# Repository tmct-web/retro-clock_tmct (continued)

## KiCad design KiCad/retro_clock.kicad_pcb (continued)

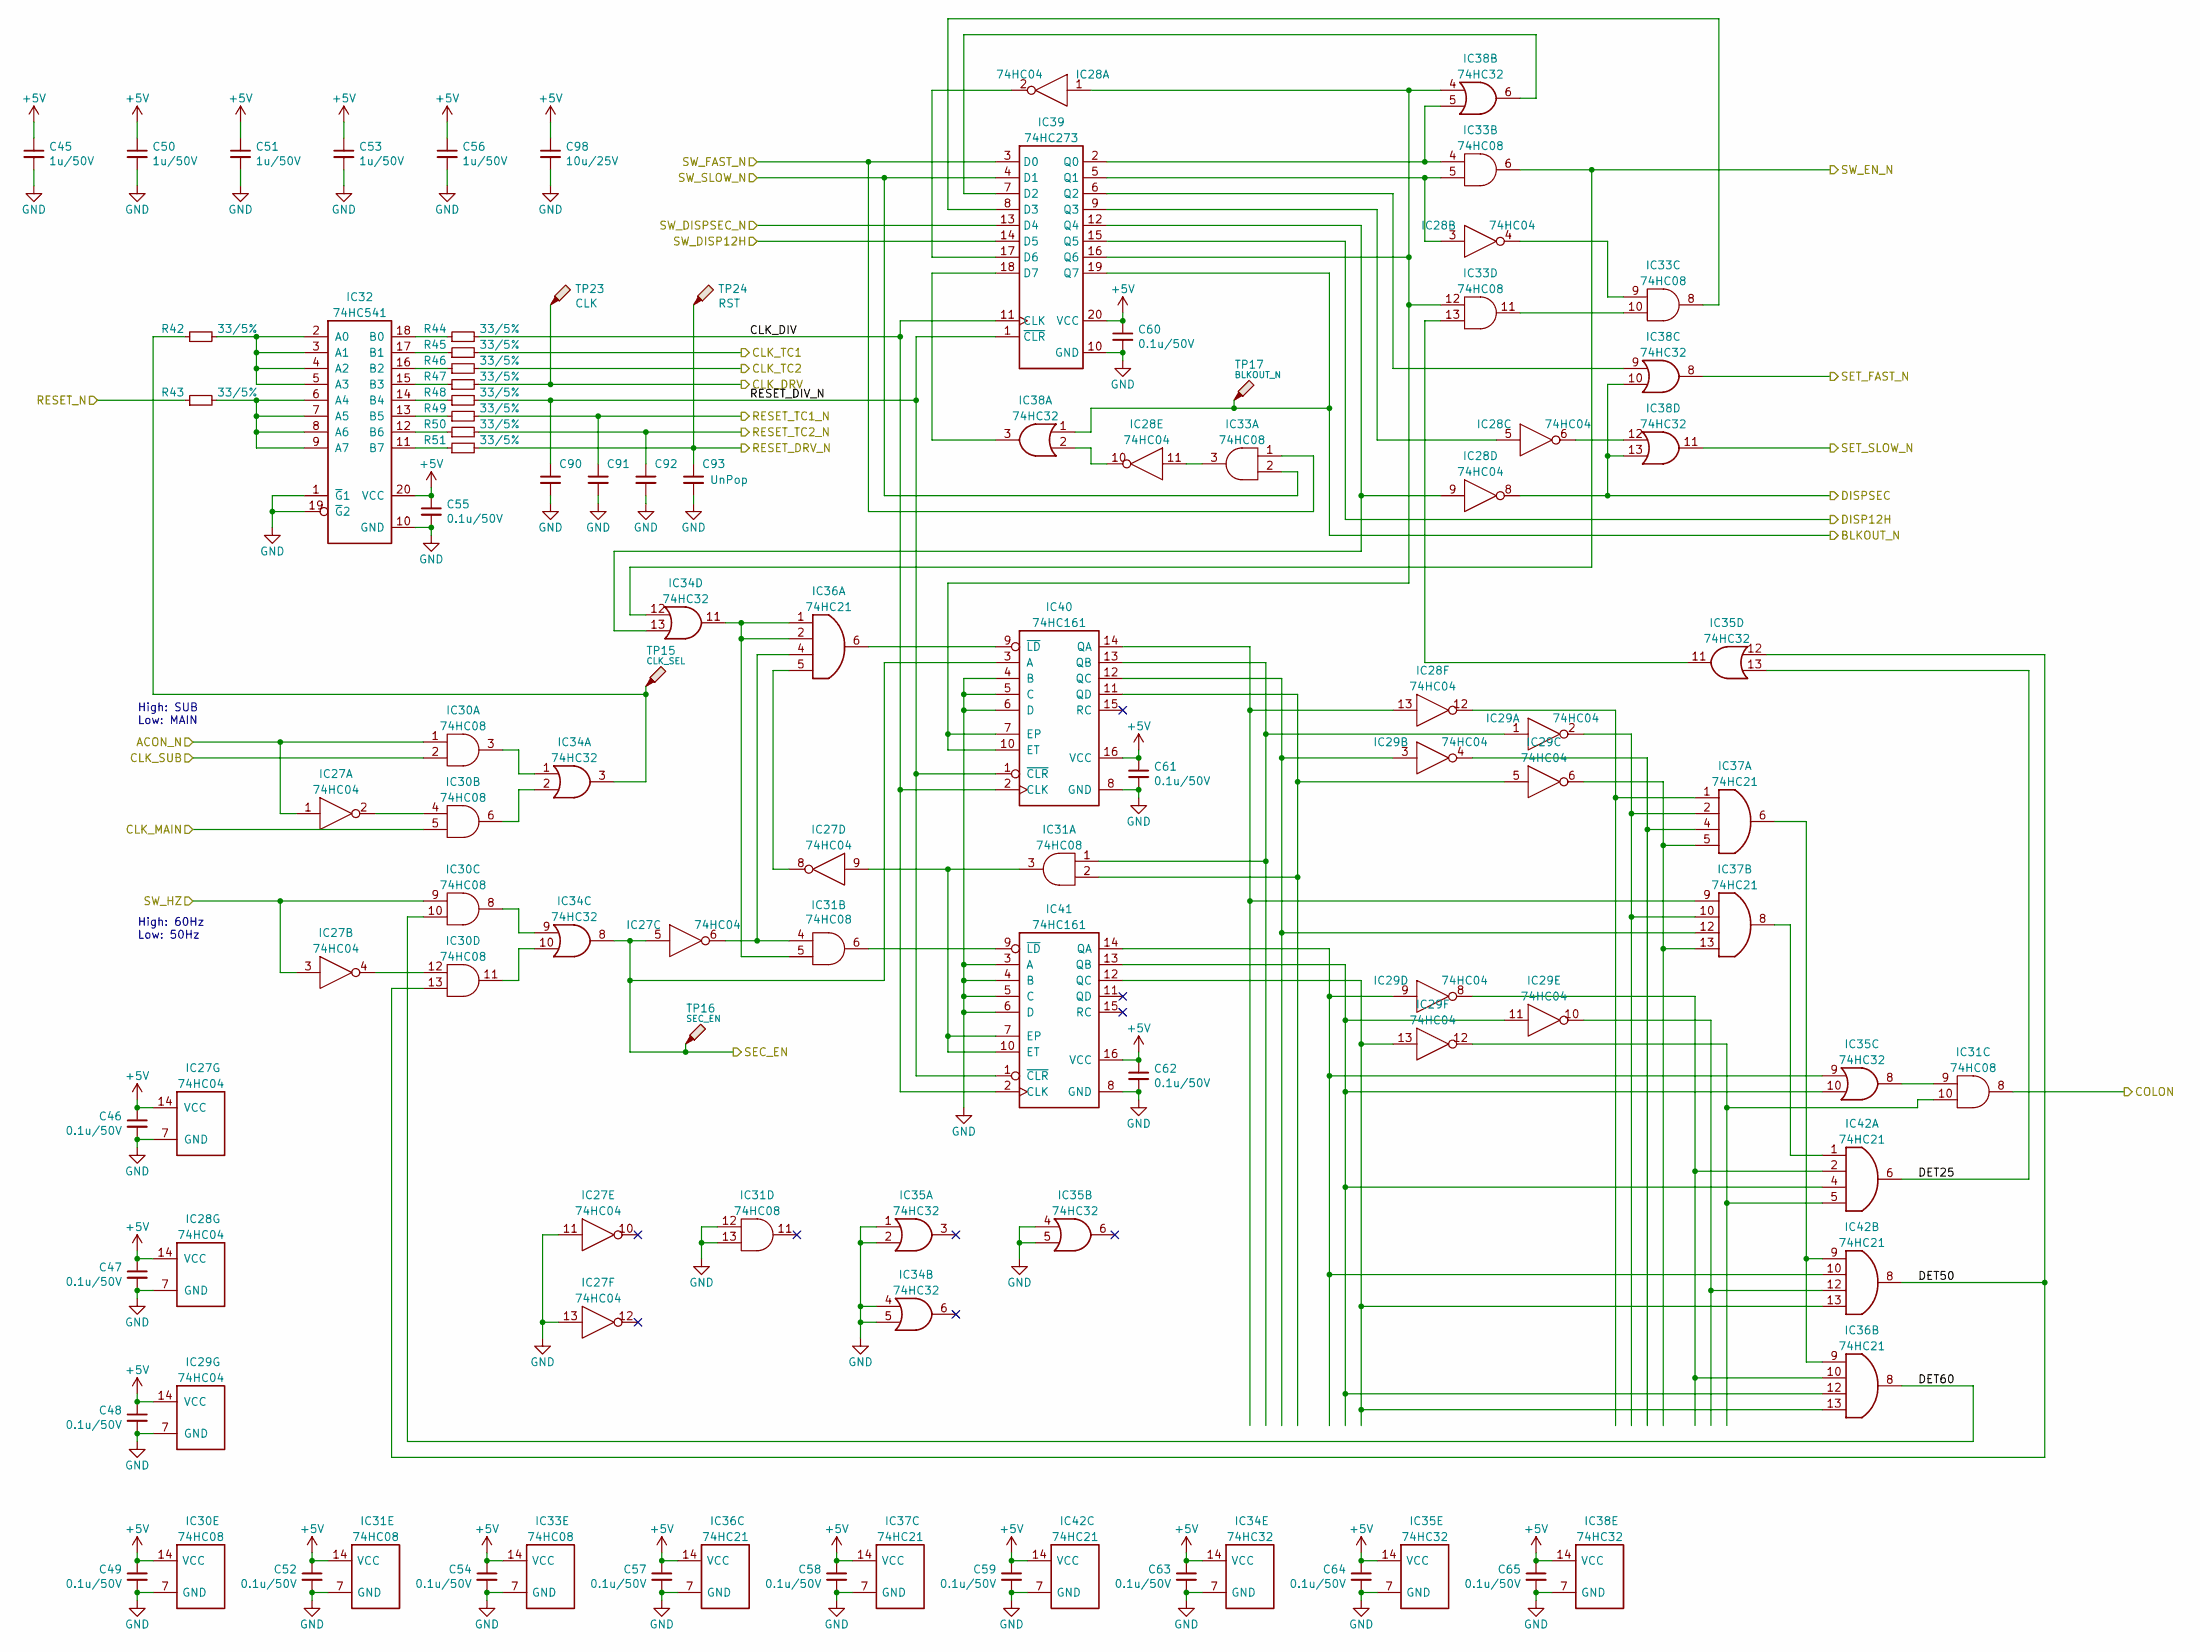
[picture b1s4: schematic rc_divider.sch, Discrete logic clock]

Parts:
C45, C50, C51, C53, C56: 1u/50V; C_Disc_P2.50mm
C46, C47, C48, C49, C52, C54, C55, C57, C58, C59, C60, C61, C62, C63, C64, C65: 0.1u/50V; C_Disc_P2.50mm
C90, C91, C92, C93: UnPop; C_Disc_P2.50mm
C98: 10u/25V; C_Disc_P5.00mm
IC27, IC28, IC29: 74HC04; DIP-14_W7.62mm_Socket_LongPads
IC30, IC31, IC33: 74HC08; DIP-14_W7.62mm_Socket_LongPads
IC32: 74HC541; DIP-20_W7.62mm_Socket_LongPads
IC34, IC35, IC38: 74HC32; DIP-14_W7.62mm_Socket_LongPads
IC36, IC37, IC42: 74HC21; DIP-14_W7.62mm_Socket_LongPads
IC39: 74HC273; DIP-20_W7.62mm_Socket_LongPads
IC40, IC41: 74HC161; DIP-16_W7.62mm_Socket_LongPads
R42, R43, R44, R45, R46, R47, R48, R49, R50, R51: 33/5%; R_Axial_P5.08mm_Horizontal
TP15: CLK_SEL; TestPoint_THTPad_1.5x1.5mm_Drill0.7mm
TP16: SEC_EN; TestPoint_THTPad_1.5x1.5mm_Drill0.7mm
TP17: BLKOUT_N; TestPoint_THTPad_1.5x1.5mm_Drill0.7mm
TP23: CLK; TestPoint_Loop_D2.60mm_Drill0.9mm_Beaded
TP24: RST; TestPoint_Loop_D2.60mm_Drill0.9mm_Beaded

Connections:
+5V: C45.1, C46.1, C47.1, C48.1, C49.1, C50.1, C51.1, C52.1, C53.1, C54.1, C55.1, C56.1, C57.1, C58.1, C59.1, C60.1, C61.1, C62.1, C63.1, C64.1, C65.1, C98.1, IC27.14 (VCC), IC28.14 (VCC), IC29.14 (VCC), IC30.14 (VCC), IC31.14 (VCC), IC32.20 (VCC), IC33.14 (VCC), IC34.14 (VCC), IC35.14 (VCC), IC36.14 (VCC), IC37.14 (VCC), IC38.14 (VCC), IC39.20 (VCC), IC40.16 (VCC), IC41.16 (VCC), IC42.14 (VCC); also elsewhere on the board
/Divider block/ACON_N: IC27.1, IC30.1; also elsewhere on the board
/Divider block/BLKOUT_N: IC38.1, IC39.19 (Q7), TP17.1; also elsewhere on the board
/Divider block/CLK_DIV: IC39.11 (CLK), IC40.2 (CLK), IC41.2 (CLK), R44.2
/Divider block/CLK_MAIN: IC30.5; also elsewhere on the board
/Divider block/CLK_SUB: IC30.2; also elsewhere on the board
/Divider block/COLON: IC31.8; also elsewhere on the board
/Divider block/DET25: IC35.13, IC42.6
/Divider block/DET50: IC30.13, IC35.12, IC42.8
/Divider block/DET60: IC30.10, IC36.8
/Divider block/DISP12H: IC39.15 (Q5); also elsewhere on the board
/Divider block/DISPSEC: IC28.8, IC38.10, IC38.13; also elsewhere on the board
/Divider block/RESET_DIV_N: C90.1, IC39.1 (~CLR), IC40.1 (~CLR), IC41.1 (~CLR), R48.2
/Divider block/RESET_DRV_N: C93.1, R51.2, TP24.1; also elsewhere on the board
/Divider block/RESET_N: R43.1; also elsewhere on the board
/Divider block/SEC_EN: IC27.5, IC34.8, IC40.3 (A), TP16.1; also elsewhere on the board
/Divider block/SET_FAST_N: IC38.8; also elsewhere on the board
/Divider block/SET_SLOW_N: IC38.11; also elsewhere on the board
/Divider block/SW_DISP12H: IC39.14 (D5); also elsewhere on the board
/Divider block/SW_DISPSEC_N: IC39.13 (D4); also elsewhere on the board
/Divider block/SW_FAST_N: IC33.1, IC39.3 (D0); also elsewhere on the board
/Divider block/SW_HZ: IC27.3, IC30.9; also elsewhere on the board
/Divider block/SW_SLOW_N: IC33.2, IC39.4 (D1); also elsewhere on the board
/Driver block/CLK: R47.2, TP23.1; also elsewhere on the board
/Time count block/CLK1: R45.2; also elsewhere on the board
/Time count block/CLK2: R46.2; also elsewhere on the board
/Time count block/RESET1_N: C91.1, R49.2; also elsewhere on the board
/Time count block/RESET2_N: C92.1, R50.2; also elsewhere on the board
/Time count block/SET_EN_N: IC33.6, IC34.12; also elsewhere on the board
GND: C45.2, C46.2, C47.2, C48.2, C49.2, C50.2, C51.2, C52.2, C53.2, C54.2, C55.2, C56.2, C57.2, C58.2, C59.2, C60.2, C61.2, C62.2, C63.2, C64.2, C65.2, C90.2, C91.2, C92.2, C93.2, C98.2, IC27.7 (GND), IC27.11, IC27.13, IC28.7 (GND), IC29.7 (GND), IC30.7 (GND), IC31.7 (GND), IC31.12, IC31.13, IC32.1 (~G~1), IC32.10 (GND), IC32.19 (~G~2), IC33.7 (GND), IC34.4, IC34.5, IC34.7 (GND), IC35.1, IC35.2, IC35.4, IC35.5, IC35.7 (GND), IC36.7 (GND), IC37.7 (GND), IC38.7 (GND), IC39.10 (GND), IC40.4 (B), IC40.5 (C), IC40.6 (D), IC40.8 (GND), IC41.3 (A), IC41.4 (B), IC41.5 (C), IC41.6 (D), IC41.8 (GND), IC42.7 (GND); also elsewhere on the board
unnamed: IC27.2, IC30.4
unnamed: IC27.4, IC30.12
unnamed: IC27.6, IC31.4, IC36.4
unnamed: IC27.8, IC36.5
unnamed: IC27.9, IC31.3, IC41.7 (EP), IC41.10 (ET)
unnamed: IC28.1, IC33.12, IC38.4, IC39.16 (Q6), IC40.7 (EP), IC40.10 (ET)
unnamed: IC28.2, IC39.17 (D6)
unnamed: IC28.3, IC33.5, IC39.5 (Q1)
unnamed: IC28.4, IC33.9
unnamed: IC28.5, IC39.9 (Q3)
unnamed: IC28.6, IC38.12
unnamed: IC28.9, IC34.13, IC39.12 (Q4)
unnamed: IC28.10, IC38.2
unnamed: IC28.11, IC33.3
unnamed: IC28.12, IC37.1
unnamed: IC28.13, IC37.9, IC40.14 (QA)
unnamed: IC29.1, IC31.1, IC40.13 (QB)
unnamed: IC29.2, IC37.2, IC37.10
unnamed: IC29.3, IC37.12, IC40.12 (QC)
unnamed: IC29.4, IC37.4
unnamed: IC29.5, IC31.2, IC40.11 (QD)
unnamed: IC29.6, IC37.5, IC37.13
unnamed: IC29.8, IC36.10, IC42.2
unnamed: IC29.9, IC35.9, IC41.14 (QA), IC42.10
unnamed: IC29.10, IC42.12
unnamed: IC29.11, IC35.10, IC36.12, IC41.13 (QB), IC42.4
unnamed: IC29.12, IC31.10, IC42.5
unnamed: IC29.13, IC36.13, IC41.12 (QC), IC42.13
unnamed: IC30.3, IC34.1
unnamed: IC30.6, IC34.2
unnamed: IC30.8, IC34.9
unnamed: IC30.11, IC34.10
unnamed: IC31.5, IC34.11, IC36.1, IC36.2
unnamed: IC31.6, IC41.9 (~LD)
unnamed: IC31.9, IC35.8
unnamed: IC32.2 (A0), IC32.3 (A1), IC32.4 (A2), IC32.5 (A3), R42.2
unnamed: IC32.6 (A4), IC32.7 (A5), IC32.8 (A6), IC32.9 (A7), R43.2
unnamed: IC32.11 (B7), R51.1
unnamed: IC32.12 (B6), R50.1
unnamed: IC32.13 (B5), R49.1
unnamed: IC32.14 (B4), R48.1
unnamed: IC32.15 (B3), R47.1
unnamed: IC32.16 (B2), R46.1
unnamed: IC32.17 (B1), R45.1
unnamed: IC32.18 (B0), R44.1
unnamed: IC33.4, IC38.5, IC39.2 (Q0)
unnamed: IC33.8, IC39.8 (D3)
unnamed: IC33.10, IC33.11
unnamed: IC33.13, IC35.11
unnamed: IC34.3, R42.1, TP15.1
unnamed: IC36.6, IC40.9 (~LD)
unnamed: IC36.9, IC37.6, IC42.9
unnamed: IC37.8, IC42.1
unnamed: IC38.3, IC39.18 (D7)
unnamed: IC38.6, IC39.7 (D2)
unnamed: IC38.9, IC39.6 (Q2)

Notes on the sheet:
High: 60Hz Low: 50Hz
High: SUB Low: MAIN

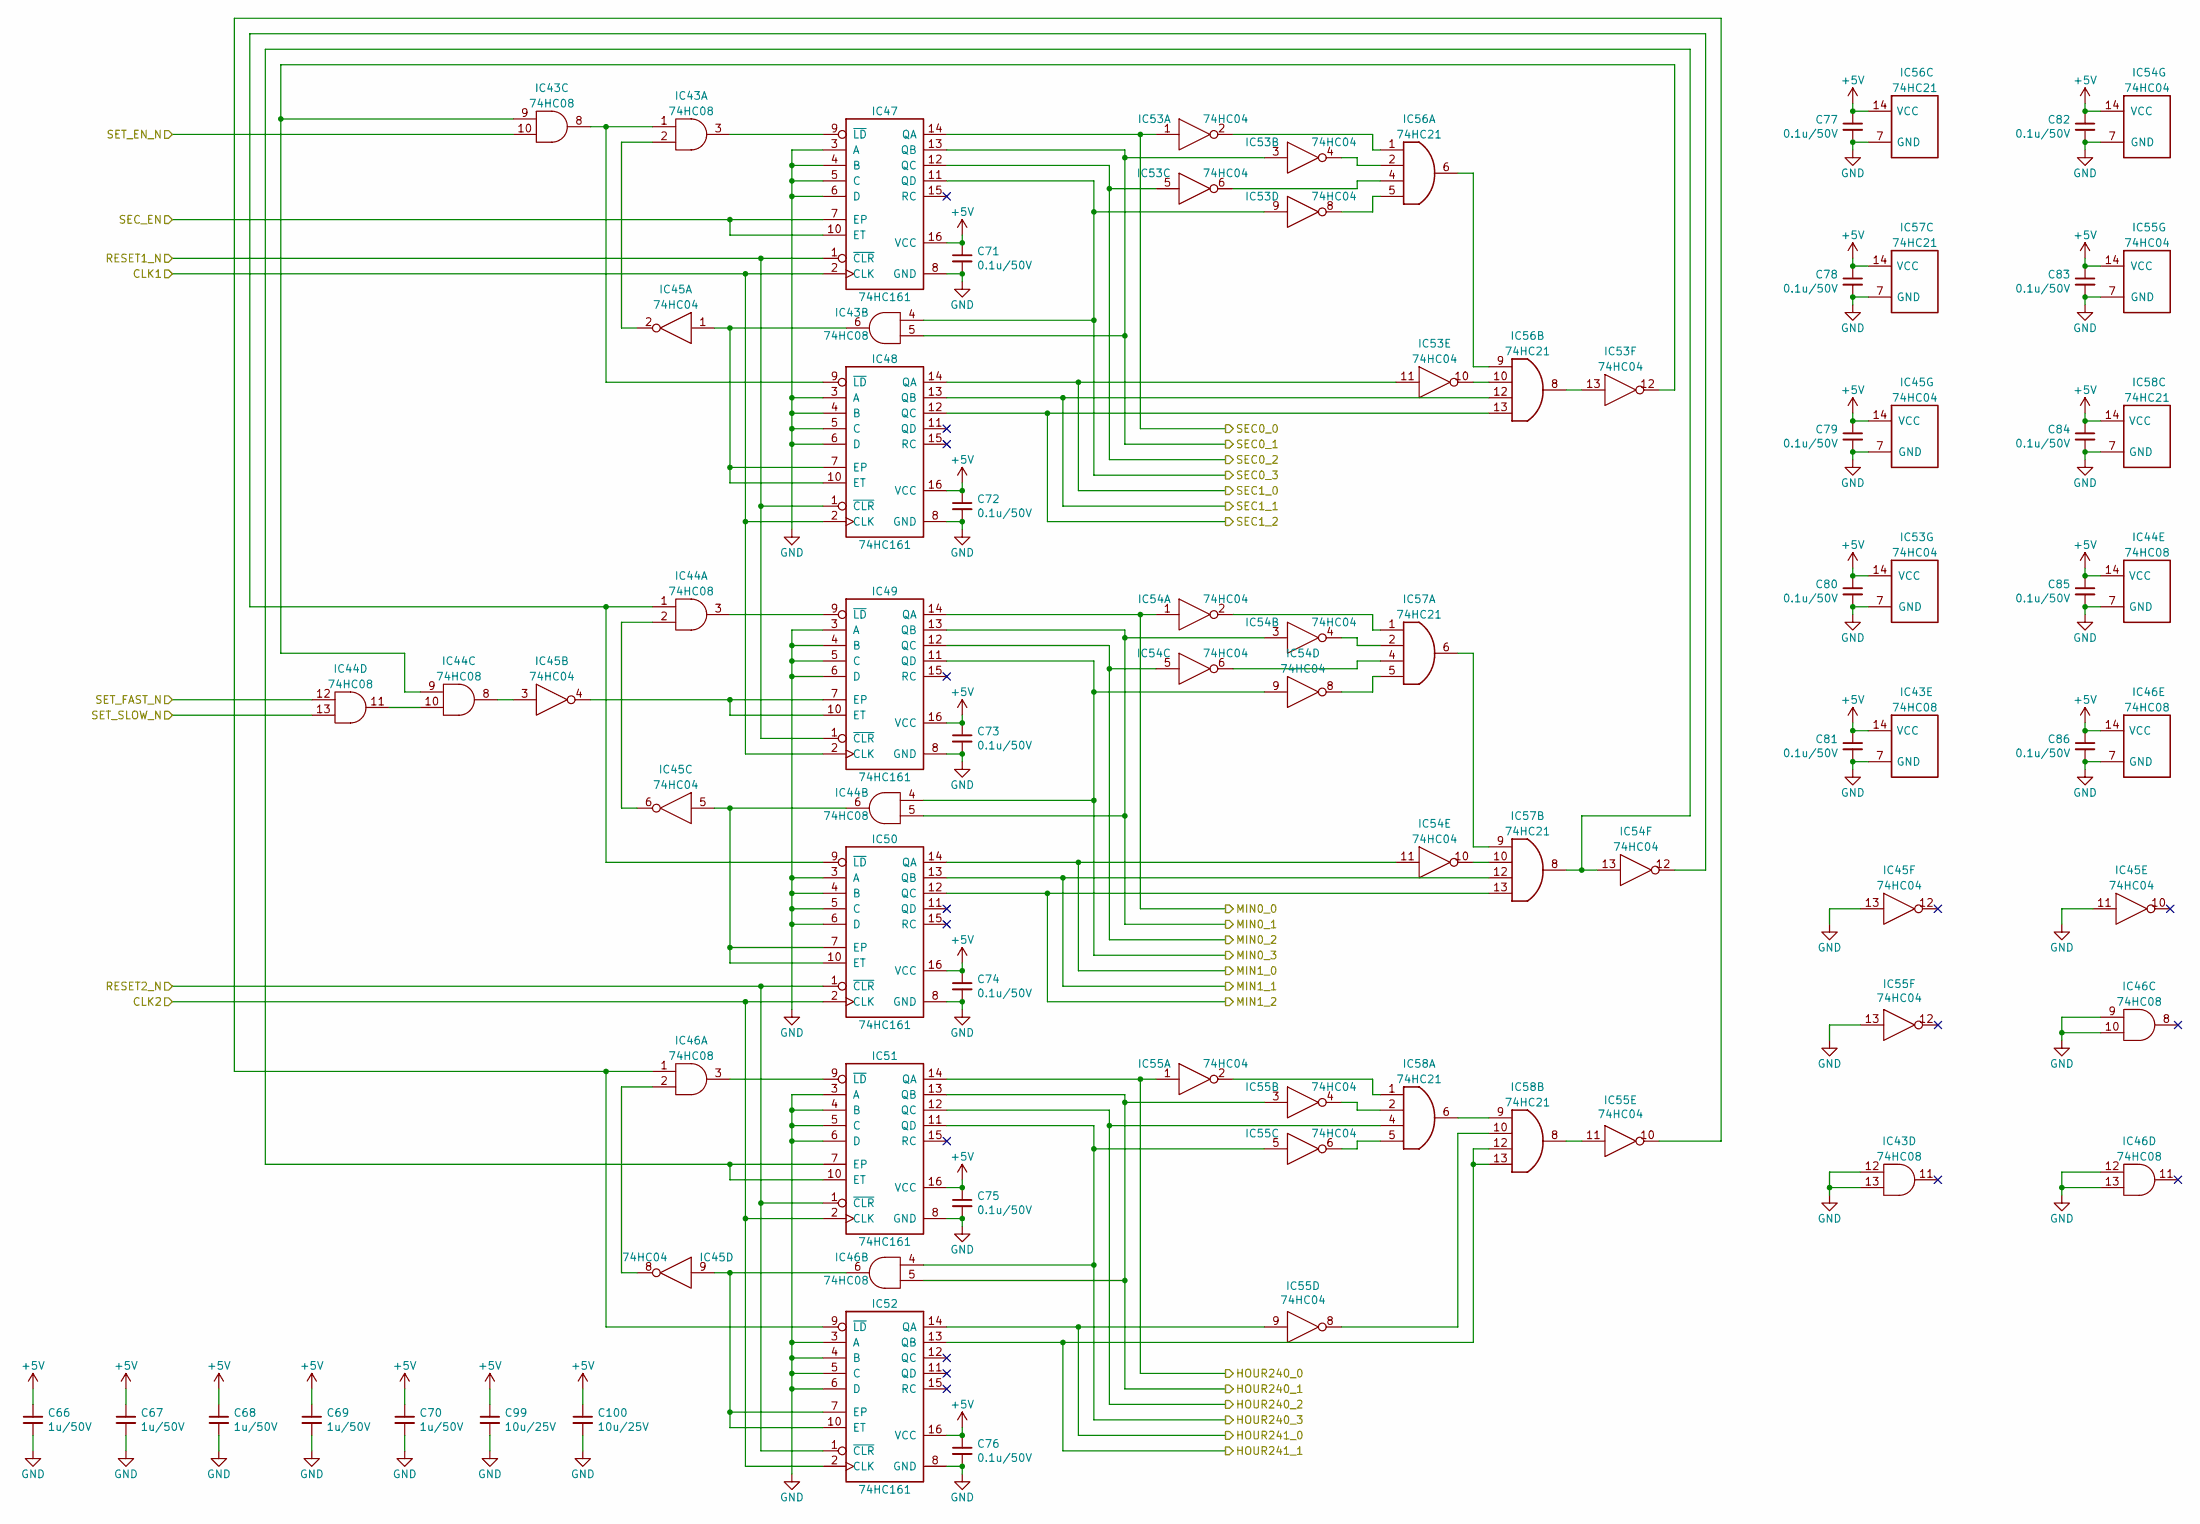
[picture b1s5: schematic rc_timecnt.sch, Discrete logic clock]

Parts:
C66, C67, C68, C69, C70: 1u/50V; C_Disc_P2.50mm
C71, C72, C73, C74, C75, C76, C77, C78, C79, C80, C81, C82, C83, C84, C85, C86: 0.1u/50V; C_Disc_P2.50mm
C99, C100: 10u/25V; C_Disc_P5.00mm
IC43, IC44, IC46: 74HC08; DIP-14_W7.62mm_Socket_LongPads
IC45, IC53, IC54, IC55: 74HC04; DIP-14_W7.62mm_Socket_LongPads
IC47, IC48, IC49, IC50, IC51, IC52: 74HC161; DIP-16_W7.62mm_Socket_LongPads
IC56, IC57, IC58: 74HC21; DIP-14_W7.62mm_Socket_LongPads

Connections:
+5V: C66.1, C67.1, C68.1, C69.1, C70.1, C71.1, C72.1, C73.1, C74.1, C75.1, C76.1, C77.1, C78.1, C79.1, C80.1, C81.1, C82.1, C83.1, C84.1, C85.1, C86.1, C99.1, C100.1, IC43.14 (VCC), IC44.14 (VCC), IC45.14 (VCC), IC46.14 (VCC), IC47.16 (VCC), IC48.16 (VCC), IC49.16 (VCC), IC50.16 (VCC), IC51.16 (VCC), IC52.16 (VCC), IC53.14 (VCC), IC54.14 (VCC), IC55.14 (VCC), IC56.14 (VCC), IC57.14 (VCC), IC58.14 (VCC); also elsewhere on the board
/Divider block/SEC_EN: IC47.7 (EP), IC47.10 (ET); also elsewhere on the board
/Divider block/SET_FAST_N: IC44.12; also elsewhere on the board
/Divider block/SET_SLOW_N: IC44.13; also elsewhere on the board
/Driver block/HOUR240_0: IC51.14 (QA), IC55.1; also elsewhere on the board
/Driver block/HOUR240_1: IC46.5, IC51.13 (QB), IC55.3; also elsewhere on the board
/Driver block/HOUR240_2: IC51.12 (QC), IC58.4; also elsewhere on the board
/Driver block/HOUR240_3: IC46.4, IC51.11 (QD), IC55.5; also elsewhere on the board
/Driver block/HOUR241_0: IC52.14 (QA), IC55.9; also elsewhere on the board
/Driver block/HOUR241_1: IC52.13 (QB), IC58.12, IC58.13; also elsewhere on the board
/Driver block/MIN0_0: IC49.14 (QA), IC54.1; also elsewhere on the board
/Driver block/MIN0_1: IC44.5, IC49.13 (QB), IC54.3; also elsewhere on the board
/Driver block/MIN0_2: IC49.12 (QC), IC54.5; also elsewhere on the board
/Driver block/MIN0_3: IC44.4, IC49.11 (QD), IC54.9; also elsewhere on the board
/Driver block/MIN1_0: IC50.14 (QA), IC54.11; also elsewhere on the board
/Driver block/MIN1_1: IC50.13 (QB), IC57.12; also elsewhere on the board
/Driver block/MIN1_2: IC50.12 (QC), IC57.13; also elsewhere on the board
/Driver block/SEC0_0: IC47.14 (QA), IC53.1; also elsewhere on the board
/Driver block/SEC0_1: IC43.5, IC47.13 (QB), IC53.3; also elsewhere on the board
/Driver block/SEC0_2: IC47.12 (QC), IC53.5; also elsewhere on the board
/Driver block/SEC0_3: IC43.4, IC47.11 (QD), IC53.9; also elsewhere on the board
/Driver block/SEC1_0: IC48.14 (QA), IC53.11; also elsewhere on the board
/Driver block/SEC1_1: IC48.13 (QB), IC56.12; also elsewhere on the board
/Driver block/SEC1_2: IC48.12 (QC), IC56.13; also elsewhere on the board
/Time count block/CLK1: IC47.2 (CLK), IC48.2 (CLK), IC49.2 (CLK); also elsewhere on the board
/Time count block/CLK2: IC50.2 (CLK), IC51.2 (CLK), IC52.2 (CLK); also elsewhere on the board
/Time count block/RESET1_N: IC47.1 (~CLR), IC48.1 (~CLR), IC49.1 (~CLR); also elsewhere on the board
/Time count block/RESET2_N: IC50.1 (~CLR), IC51.1 (~CLR), IC52.1 (~CLR); also elsewhere on the board
/Time count block/SET_EN_N: IC43.10; also elsewhere on the board
GND: C66.2, C67.2, C68.2, C69.2, C70.2, C71.2, C72.2, C73.2, C74.2, C75.2, C76.2, C77.2, C78.2, C79.2, C80.2, C81.2, C82.2, C83.2, C84.2, C85.2, C86.2, C99.2, C100.2, IC43.7 (GND), IC43.12, IC43.13, IC44.7 (GND), IC45.7 (GND), IC45.11, IC45.13, IC46.7 (GND), IC46.9, IC46.10, IC46.12, IC46.13, IC47.3 (A), IC47.4 (B), IC47.5 (C), IC47.6 (D), IC47.8 (GND), IC48.3 (A), IC48.4 (B), IC48.5 (C), IC48.6 (D), IC48.8 (GND), IC49.3 (A), IC49.4 (B), IC49.5 (C), IC49.6 (D), IC49.8 (GND), IC50.3 (A), IC50.4 (B), IC50.5 (C), IC50.6 (D), IC50.8 (GND), IC51.3 (A), IC51.4 (B), IC51.5 (C), IC51.6 (D), IC51.8 (GND), IC52.3 (A), IC52.4 (B), IC52.5 (C), IC52.6 (D), IC52.8 (GND), IC53.7 (GND), IC54.7 (GND), IC55.7 (GND), IC55.13, IC56.7 (GND), IC57.7 (GND), IC58.7 (GND); also elsewhere on the board
unnamed: IC43.1, IC43.8, IC48.9 (~LD)
unnamed: IC43.2, IC45.2
unnamed: IC43.3, IC47.9 (~LD)
unnamed: IC43.6, IC45.1, IC48.7 (EP), IC48.10 (ET)
unnamed: IC43.9, IC44.9, IC53.12
unnamed: IC44.1, IC50.9 (~LD), IC54.12
unnamed: IC44.2, IC45.6
unnamed: IC44.3, IC49.9 (~LD)
unnamed: IC44.6, IC45.5, IC50.7 (EP), IC50.10 (ET)
unnamed: IC44.8, IC45.3
unnamed: IC44.10, IC44.11
unnamed: IC45.4, IC49.7 (EP), IC49.10 (ET)
unnamed: IC45.8, IC46.2
unnamed: IC45.9, IC46.6, IC52.7 (EP), IC52.10 (ET)
unnamed: IC46.1, IC52.9 (~LD), IC55.10
unnamed: IC46.3, IC51.9 (~LD)
unnamed: IC51.7 (EP), IC51.10 (ET), IC54.13, IC57.8
unnamed: IC53.2, IC56.1
unnamed: IC53.4, IC56.2
unnamed: IC53.6, IC56.4
unnamed: IC53.8, IC56.5
unnamed: IC53.10, IC56.10
unnamed: IC53.13, IC56.8
unnamed: IC54.2, IC57.1
unnamed: IC54.4, IC57.2
unnamed: IC54.6, IC57.4
unnamed: IC54.8, IC57.5
unnamed: IC54.10, IC57.10
unnamed: IC55.2, IC58.1
unnamed: IC55.4, IC58.2
unnamed: IC55.6, IC58.5
unnamed: IC55.8, IC58.10
unnamed: IC55.11, IC58.8
unnamed: IC56.6, IC56.9
unnamed: IC57.6, IC57.9
unnamed: IC58.6, IC58.9

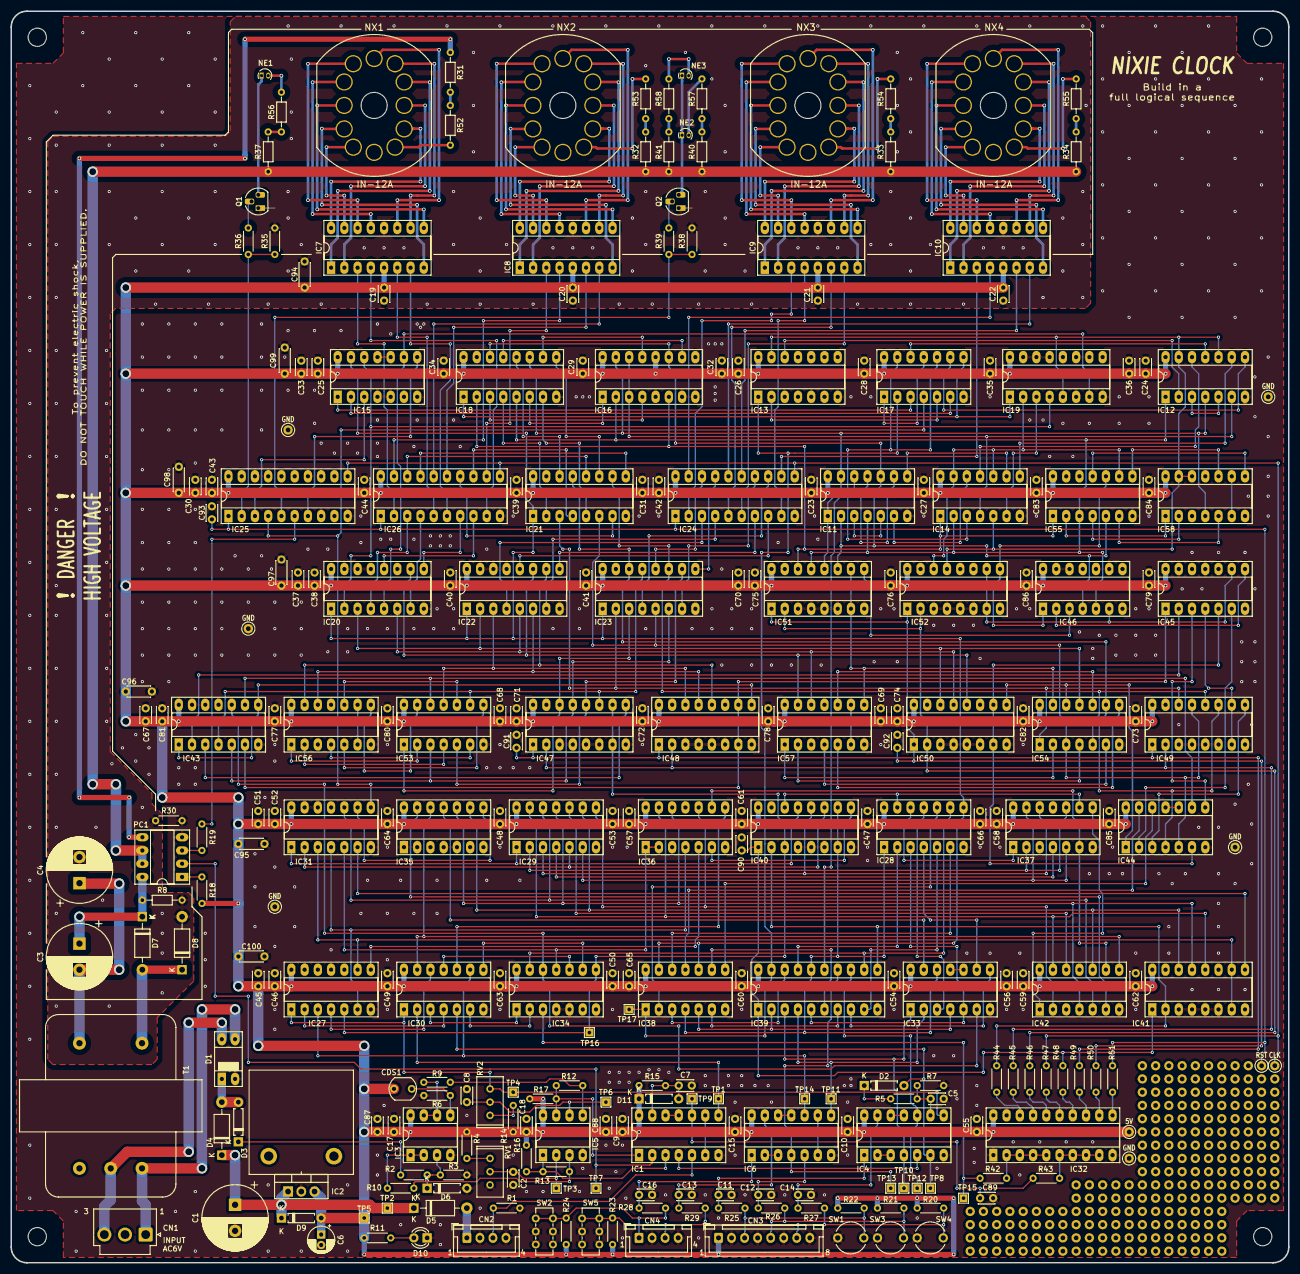
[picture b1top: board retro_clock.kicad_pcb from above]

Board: 2 copper layers, 245.0 x 240.0 mm, 276 parts (0 on the bottom side), 316 nets.

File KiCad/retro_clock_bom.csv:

Reference,Quantity,Value,Remarks
C1,1,1500u/25V,???????
C11;C12;C14;C13;C8;C17;C18;C2;C16;C9;C15;C10;C19;C20;C21;C22;C28;C24;C26;C29;C27;C25;C23;C34;C35;C41;C40;C42;C39;C38;C44;C43;C60;C61;C62;C55;C49;C63;C46;C64;C54;C48;C47;C52;C59;C65;C58;C57;C71;C72;C77;C82;C78;C83;C79;C84;C80;C85;C81;C86;C73;C74;C75;C76,64,0.1u/50V,??????????
C3;C4,2,10u/400V,???????
C5;C7;C87;C88;C30;C32;C31;C33;C36;C37;C45;C50;C53;C56;C51;C66;C67;C68;C69;C70,20,1u/50V,??????????
C6,1,100u/16V,???????
C94;C95;C96;C97;C98;C99;C100,7,10u/25V,??????????
CDS1,1,GL5528,
CN1,1,B3P-VH(LF)(SN),JST
CN3,1,XH_B8B-XH-A,JST
CN4;CN2,2,XH_B4B-XH-A,JST
D1,1,S1ZB,
D10,1,LED,
D4;D5;D7;D8,4,UF2010,
D6,1,GDZJ4.7C,
D9;D3;D11;D2,4,BAT43,
IC1;IC4;IC6,3,74HC14,
IC13;IC27;IC29;IC28;IC45;IC53;IC54;IC55,8,74HC04,
IC15;IC12;IC11;IC38;IC35;IC34,6,74HC32,
IC16,1,74HC283,
IC17;IC14;IC33;IC31;IC30;IC43;IC44;IC46,8,74HC08,
IC2,1,LM2940T-5.0,
IC20;IC21;IC22;IC23;IC18;IC19,6,74HC157,
IC25;IC26;IC24;IC39,4,74HC273,
IC3,1,NJU7043,
IC32,1,74HC541,
IC36;IC42;IC37;IC56;IC57;IC58,6,74HC21,
IC40;IC41;IC47;IC48;IC49;IC50;IC51;IC52,8,74HC161,
IC5,1,LM393,
IC7;IC8;IC9;IC10,4,K155ID1,
NE1;NE2;NE3,3,Lamp_Neon,????
NX1;NX2;NX3;NX4,4,IN-12A,?????(????????)
PC1,1,TLP222G-2,
Q1;Q2,2,MPSA42,
R11,1,2.7k/5%,
R13;R12;R7;R15;R35;R38,6,100k/5%,
R14;R3;R22;R21;R20;R23;R24;R5,8,4.7k/5%,
R17;R16;R1;R36;R39,5,10k/5%,
R18;R19,2,330/5%,
R2,1,8.2k/5%,
R25;R26;R27;R28;R10;R9;R29,7,1k/5%,
R30,1,0,
R31;R32;R33;R34;R53;R54;R55;R52,8,20k/5%/0.5W,
R37;R40;R41,3,200k/5%/0.5W,
R4,1,6.8k/5%,
R44;R45;R46;R47;R48;R49;R50;R51;R42;R43,10,33/5%,
R56;R57;R58,3,33k/5%/0.5W,
R6,1,3.3k/5%,
R8,1,1M/5%/0.5W,
RV2;RV1,2,Bourns_3296W/10k,????????
SW1;SW3;SW4,3,TVDT18-050CB-T,???????????
SW2;SW5,2,IS-2235-G,????????????
T1,1,HP-612,????????
,,HT-1205,??????
C89;C90;C93;C91;C92,5,UnPop,???

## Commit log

2020-12-13 Update README.md
    Add web site link.
2020-12-13 Project 1st commit
2021-10-17 Update README.md
    Update README.md
2022-02-05 Review files and 'readme.md'
